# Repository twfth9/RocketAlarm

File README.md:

# RocketAlarm
Battery powered buzzer alarm for use in model rocketry

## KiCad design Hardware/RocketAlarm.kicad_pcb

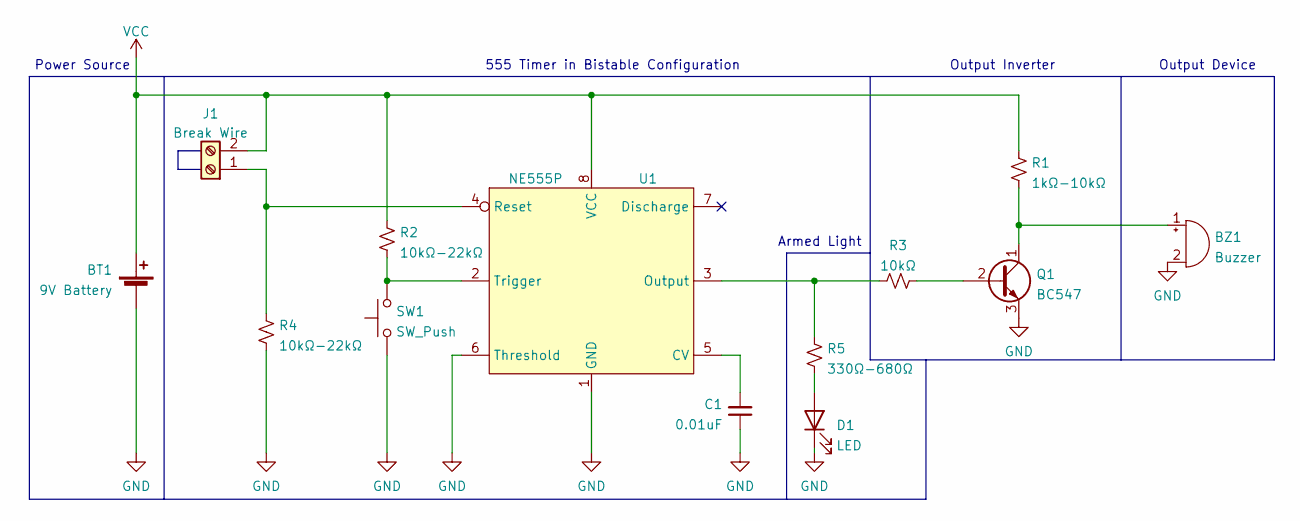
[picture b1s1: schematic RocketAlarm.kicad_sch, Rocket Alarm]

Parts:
BT1: 9V Battery; BatteryHolder_9V
BZ1: Buzzer; Buzzer_JST_Header
C1: 0.01uF; C_Disc_D5.0mm_W2.5mm_P5.00mm
D1: LED; LED_D5.0mm
J1: Break Wire; TerminalBlock_Phoenix_MKDS-1,5-2_1x02_P5.00mm_Horizontal
Q1: BC547; TO-92_Inline
R1: 1kΩ-10kΩ; R_Axial_DIN0309_L9.0mm_D3.2mm_P2.54mm_Vertical
R2, R4: 10kΩ-22kΩ; R_Axial_DIN0309_L9.0mm_D3.2mm_P2.54mm_Vertical
R3: 10kΩ; R_Axial_DIN0309_L9.0mm_D3.2mm_P2.54mm_Vertical
R5: 330Ω-680Ω; R_Axial_DIN0309_L9.0mm_D3.2mm_P2.54mm_Vertical
SW1: SW_Push; SW_PUSH_6mm_H8mm
U1: NE555P; DIP-8_W7.62mm

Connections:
GND: BT1.2 (-), BZ1.2 (+), C1.1, D1.1 (K), Q1.3 (E), R4.2, SW1.1, U1.1 (GND), U1.6 (Threshold); also elsewhere on the board
unnamed 1: BZ1.1 (-), Q1.1 (C), R1.1; also elsewhere on the board
unnamed: C1.2, U1.5 (CV)
unnamed: D1.2 (A), R5.2
unnamed: J1.1, R4.1, U1.4 (Reset)
unnamed: Q1.2 (B), R3.2
unnamed: R2.2, SW1.2, U1.2 (Trigger)
unnamed: R3.1, R5.1, U1.3 (Output)
VCC: BT1.1 (+), J1.2, R1.2, R2.1, U1.8 (VCC)

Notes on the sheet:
555 Timer in Bistable Configuration
Armed Light
Output Inverter
Power Source
Output Device

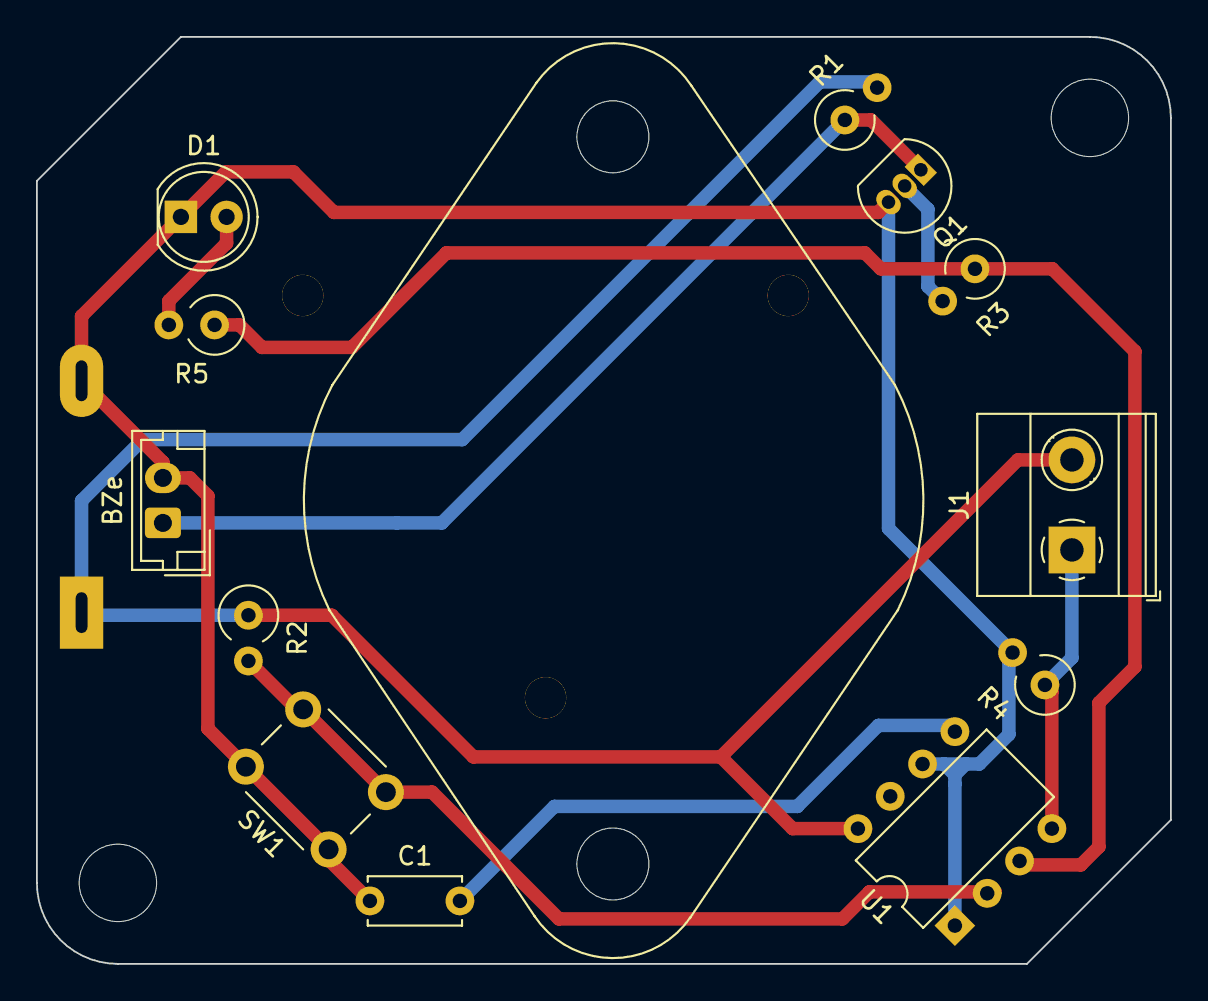
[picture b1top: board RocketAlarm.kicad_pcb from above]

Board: 2 copper layers, 63.0 x 51.5 mm, 13 parts (1 on the bottom side), 9 nets.

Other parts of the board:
BZe: Buzzer; Buzzer_JST_Header

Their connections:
GND: BZe.2 (+); also elsewhere on the board
unnamed 1: BZe.1 (-); also elsewhere on the board

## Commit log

2023-03-18 Created Rocket Alarm and initial PCB
